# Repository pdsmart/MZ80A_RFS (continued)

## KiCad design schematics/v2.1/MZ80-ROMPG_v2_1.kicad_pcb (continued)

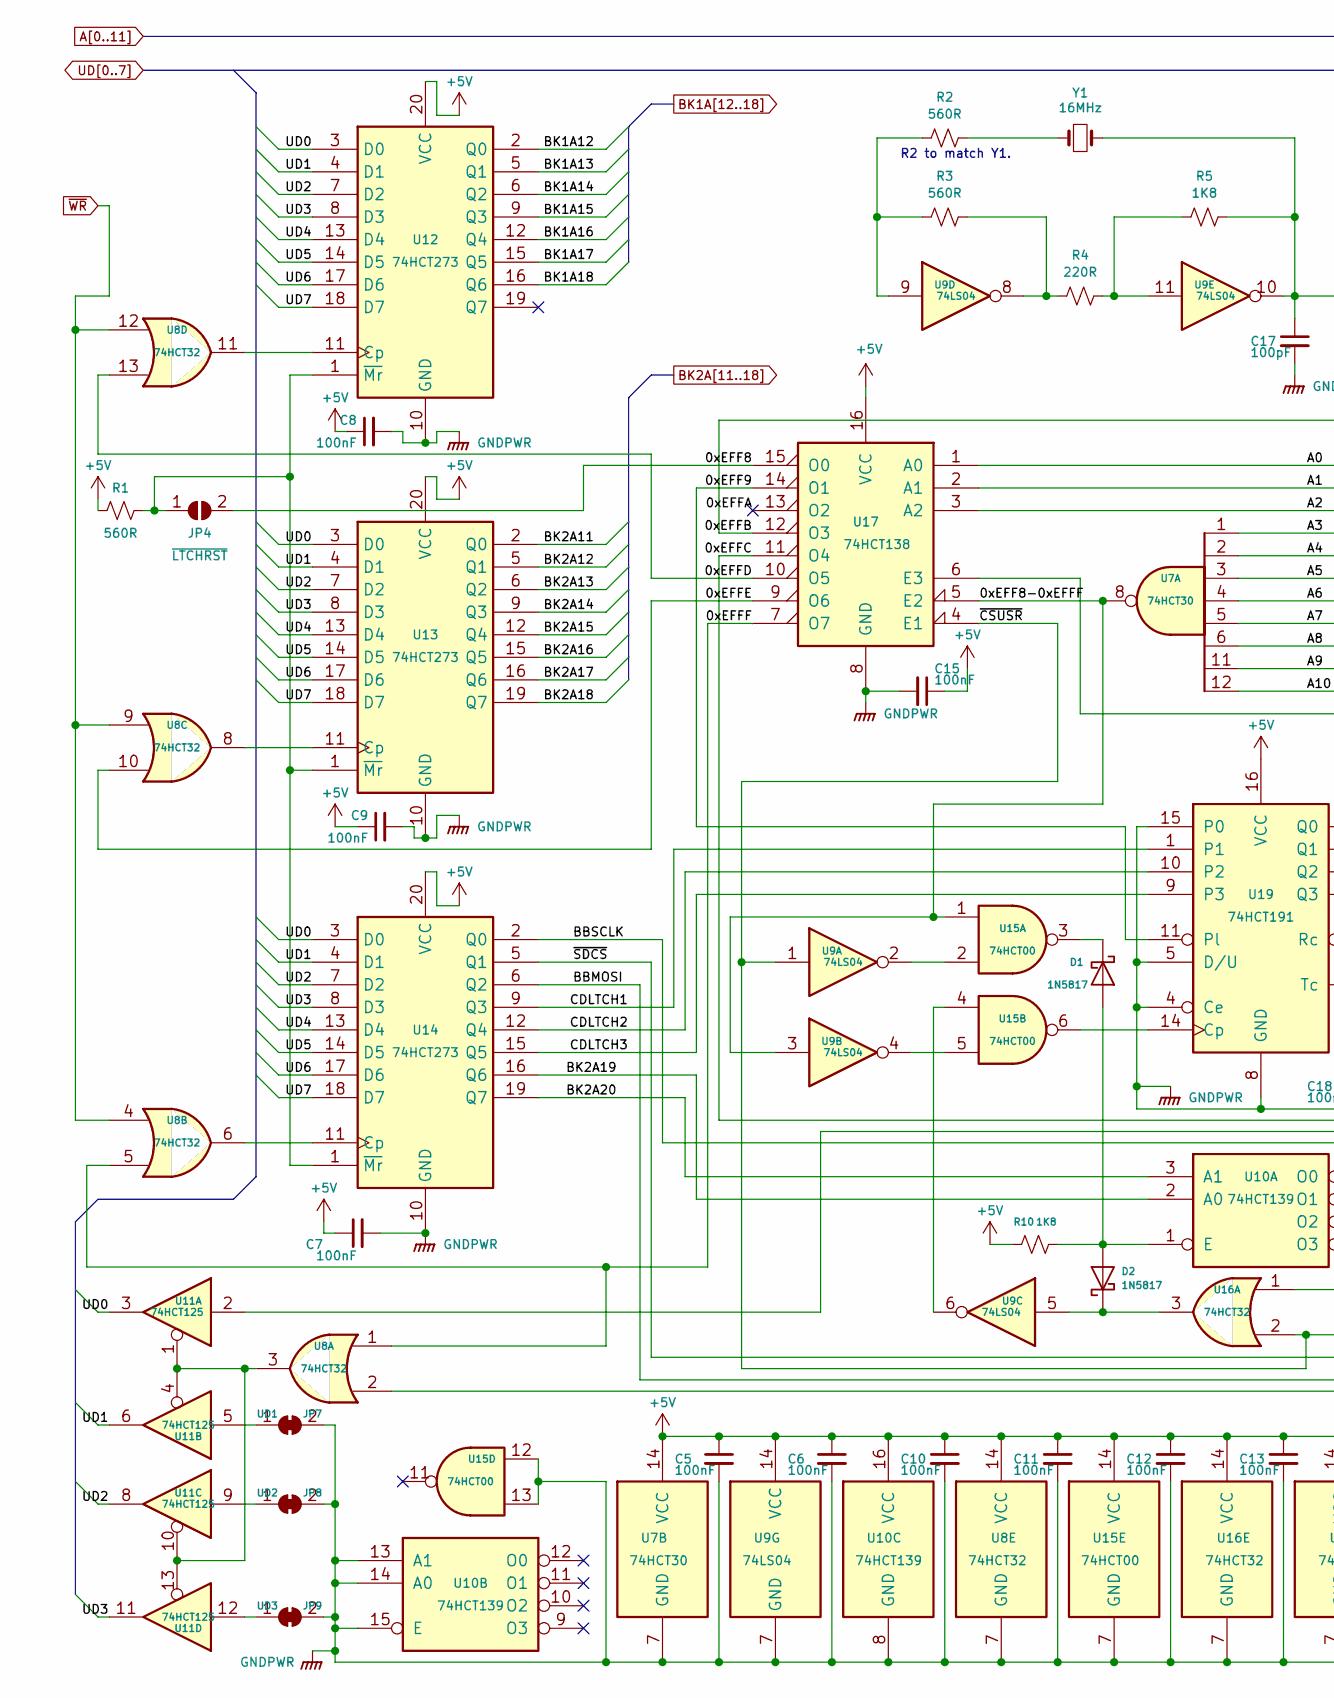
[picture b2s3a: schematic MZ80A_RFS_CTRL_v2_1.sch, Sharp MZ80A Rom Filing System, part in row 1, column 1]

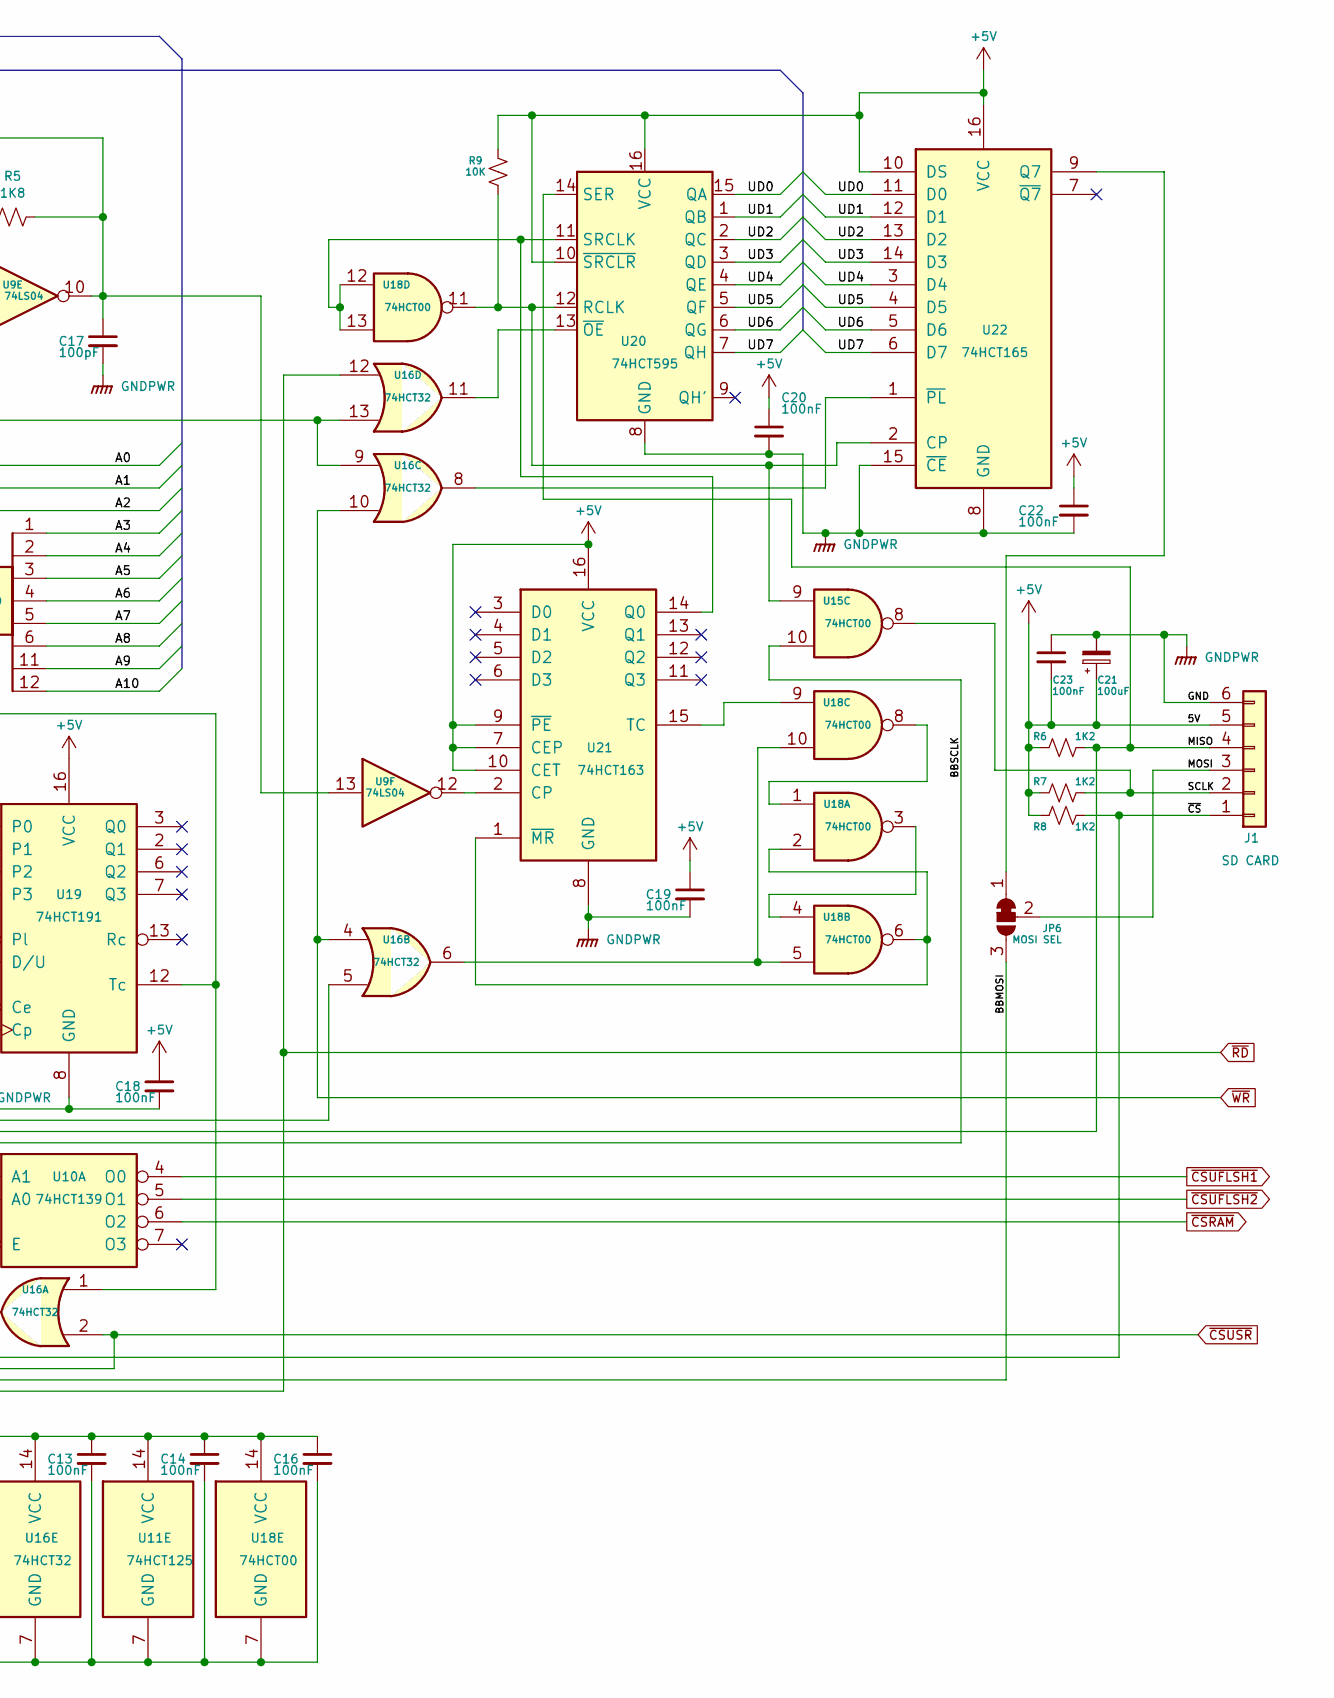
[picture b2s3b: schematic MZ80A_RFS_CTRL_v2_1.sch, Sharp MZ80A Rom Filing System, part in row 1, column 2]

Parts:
C5, C6, C7, C8, C9, C10, C11, C12, C13, C14, C15, C16, C18, C19, C20, C21, C22: 100nF; C_0805_2012Metric_Pad1.15x1.40mm_HandSolder
C17: 100pF; C_0805_2012Metric_Pad1.15x1.40mm_HandSolder
C23: 100uF; C_1206_3216Metric_Pad1.42x1.75mm_HandSolder
D1, D2: 1N5817; D_SOD-123
J1: SD CARD; PinSocket_1x06_P2.54mm_Horizontal
JP4: ~LTCHRST~; SolderJumper-2_P1.3mm_Bridged_Pad1.0x1.5mm
JP6: MOSI SEL; SolderJumper-3_P1.3mm_Bridged2Bar12_Pad1.0x1.5mm
JP7: UD1; SolderJumper-2_P1.3mm_Bridged_Pad1.0x1.5mm
JP8: UD2; SolderJumper-2_P1.3mm_Bridged_Pad1.0x1.5mm
JP9: UD3; SolderJumper-2_P1.3mm_Bridged_Pad1.0x1.5mm
R1, R2, R3: 560R; R_0805_2012Metric_Pad1.15x1.40mm_HandSolder
R4: 220R; R_0805_2012Metric_Pad1.15x1.40mm_HandSolder
R5, R10: 1K8; R_0805_2012Metric_Pad1.15x1.40mm_HandSolder
R6, R7, R8: 1K2; R_0805_2012Metric_Pad1.15x1.40mm_HandSolder
R9: 10K; R_0805_2012Metric_Pad1.15x1.40mm_HandSolder
U7: 74HCT30; SOIC-14_3.9x8.7mm_P1.27mm
U8, U16: 74HCT32; SOIC-14_3.9x8.7mm_P1.27mm
U9: 74LS04; SOIC-14_3.9x8.7mm_P1.27mm
U10: 74HCT139; SOIC-16_3.9x9.9mm_P1.27mm
U11: 74HCT125; SOIC-14_3.9x8.7mm_P1.27mm
U12, U13, U14: 74HCT273; SOIC-20W_7.5x12.8mm_P1.27mm
U15, U18: 74HCT00; SOIC-14_3.9x8.7mm_P1.27mm
U17: 74HCT138; SOIC-16_3.9x9.9mm_P1.27mm
U19: 74HCT191; SOIC-16_3.9x9.9mm_P1.27mm
U20: 74HCT595; SOIC-16_3.9x9.9mm_P1.27mm
U21: 74HCT163; SOIC-16_3.9x9.9mm_P1.27mm
U22: 74HCT165; SOIC-16_3.9x9.9mm_P1.27mm
Y1: 16MHz; Crystal_SMD_Abracon_ABM3-2Pin_5.0x3.2mm

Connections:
+5V: C5.1, C6.1, C7.1, C8.1, C9.1, C10.1, C11.1, C12.1, C13.1, C14.1, C15.1, C16.1, C18.1, C19.1, C20.1, C21.2, C22.1, C23.1, J1.5, R1.2, R6.2, R7.2, R8.2, R9.2, R10.2, U7.14 (VCC), U8.14 (VCC), U9.14 (VCC), U10.16 (VCC), U11.14 (VCC), U12.20 (VCC), U13.20 (VCC), U14.20 (VCC), U15.14 (VCC), U16.14 (VCC), U17.16 (VCC), U18.14 (VCC), U19.16 (VCC), U20.10 (~SRCLR), U20.16 (VCC), U21.7 (CEP), U21.9 (~PE), U21.10 (CET), U21.16 (VCC), U22.10 (DS), U22.16 (VCC); also elsewhere on the board
/CONTROLLOGIC/0xEFF8: JP4.2 (B), U17.15 (O0)
/CONTROLLOGIC/0xEFF8-0xEFFF: U7.8, U9.3, U15.1, U17.5 (E2)
/CONTROLLOGIC/0xEFF9: U17.14 (O1), U19.11 (Pl)
/CONTROLLOGIC/0xEFFA: U17.13 (O2)
/CONTROLLOGIC/0xEFFB: U16.9, U16.13, U17.12 (O3)
/CONTROLLOGIC/0xEFFC: U16.5, U17.11 (O4)
/CONTROLLOGIC/0xEFFD: U8.13, U17.10 (O5)
/CONTROLLOGIC/0xEFFE: U8.10, U17.9 (O6)
/CONTROLLOGIC/0xEFFF: U8.1, U8.5, U17.7 (O7)
/CONTROLLOGIC/BBMOSI: JP6.3 (B), U14.6 (Q2)
/CONTROLLOGIC/BBSCLK: U14.2 (Q0), U15.10
/CONTROLLOGIC/BK2A19: U10.2 (A0), U14.16 (Q6)
/CONTROLLOGIC/BK2A20: U10.3 (A1), U14.19 (Q7)
/CONTROLLOGIC/CDLTCH1: U14.9 (Q3), U19.1
/CONTROLLOGIC/CDLTCH2: U14.12 (Q4), U19.10 (P2)
/CONTROLLOGIC/CDLTCH3: U14.15 (Q5), U19.9 (P3)
/CONTROLLOGIC/MISO: J1.4, R6.1, U11.2, U20.14 (SER)
/CONTROLLOGIC/MOSI: J1.3, JP6.2 (C)
/CONTROLLOGIC/SCLK: J1.2, R7.1, U15.8
/CONTROLLOGIC/~CS~: J1.1, R8.1, U14.5 (Q1)
A0: U17.1 (A0); also elsewhere on the board
A1: U17.2 (A1); also elsewhere on the board
A2: U17.3 (A2); also elsewhere on the board
A3: U7.1; also elsewhere on the board
A4: U7.2; also elsewhere on the board
A5: U7.3; also elsewhere on the board
A6: U7.4; also elsewhere on the board
A7: U7.5; also elsewhere on the board
A8: U7.6; also elsewhere on the board
A9: U7.11; also elsewhere on the board
A10: U7.12; also elsewhere on the board
BK1A12: U12.2 (Q0); also elsewhere on the board
BK1A13: U12.5 (Q1); also elsewhere on the board
BK1A14: U12.6 (Q2); also elsewhere on the board
BK1A15: U12.9 (Q3); also elsewhere on the board
BK1A16: U12.12 (Q4); also elsewhere on the board
BK1A17: U12.15 (Q5); also elsewhere on the board
BK1A18: U12.16 (Q6); also elsewhere on the board
BK2A11: U13.2 (Q0); also elsewhere on the board
BK2A12: U13.5 (Q1); also elsewhere on the board
BK2A13: U13.6 (Q2); also elsewhere on the board
BK2A14: U13.9 (Q3); also elsewhere on the board
BK2A15: U13.12 (Q4); also elsewhere on the board
BK2A16: U13.15 (Q5); also elsewhere on the board
BK2A17: U13.16 (Q6); also elsewhere on the board
BK2A18: U13.19 (Q7); also elsewhere on the board
GNDPWR: C5.2, C6.2, C7.2, C8.2, C9.2, C10.2, C11.2, C12.2, C13.2, C14.2, C15.2, C16.2, C17.2, C18.2, C19.2, C20.2, C21.1, C22.2, C23.2, J1.6, JP7.2 (B), JP8.2 (B), JP9.2 (B), U7.7 (GND), U8.7 (GND), U9.7 (GND), U10.8 (GND), U10.13 (A1), U10.14 (A0), U10.15 (E), U11.7 (GND), U12.10 (GND), U13.10 (GND), U14.10 (GND), U15.7 (GND), U15.12, U15.13, U16.7 (GND), U17.8 (GND), U18.7 (GND), U19.4 (Ce), U19.5 (D/U), U19.8 (GND), U19.15 (P0), U20.8 (GND), U21.8 (GND), U22.8 (GND), U22.15 (~CE); also elsewhere on the board
unnamed: C17.1, R5.1, U9.10, U9.13, Y1.2
unnamed: D1.1 (K), U15.3
unnamed: D1.2 (A), D2.2 (A), R10.1, U10.1 (E)
unnamed: D2.1 (K), U9.5, U16.3
unnamed: JP4.1 (A), R1.1, U12.1 (~Mr), U13.1 (~Mr), U14.1 (~Mr)
unnamed: JP6.1 (A), U22.9 (Q7)
unnamed: JP7.1 (A), U11.5
unnamed: JP8.1 (A), U11.9
unnamed: JP9.1 (A), U11.12
unnamed: R2.1, Y1.1
unnamed: R2.2, R3.2, U9.9
unnamed: R3.1, R4.2, U9.8
unnamed: R4.1, R5.2, U9.11
unnamed: R9.1, U15.9, U18.11, U20.12 (RCLK), U22.2 (CP)
unnamed: U8.3, U11.1, U11.4, U11.10, U11.13
unnamed: U8.11, U12.11 (Cp)
unnamed: U8.8, U13.11 (Cp)
unnamed: U8.6, U14.11 (Cp)
unnamed: U9.2, U15.2
unnamed: U9.6, U15.4
unnamed: U9.4, U15.5
unnamed: U15.6, U19.14 (Cp)
unnamed: U16.1, U17.6 (E3), U19.12 (Tc)
unnamed: U16.6, U18.5, U18.10
unnamed: U16.8, U22.1 (~PL)
unnamed: U16.11, U20.13 (~OE)
unnamed: U18.1, U18.8
unnamed: U18.2, U18.6, U21.1 (~MR)
unnamed: U18.3, U18.4
unnamed: U18.9, U21.15 (TC)
unnamed: U18.12, U18.13, U20.11 (SRCLK), U21.14 (Q0)
unnamed: U9.12, U21.2 (CP)
UD0: U11.3, U12.3 (D0), U13.3 (D0), U14.3 (D0), U20.15 (QA), U22.11 (D0); also elsewhere on the board
UD1: U11.6, U12.4 (D1), U13.4 (D1), U14.4 (D1), U20.1 (QB), U22.12 (D1); also elsewhere on the board
UD2: U11.8, U12.7 (D2), U13.7 (D2), U14.7 (D2), U20.2 (QC), U22.13 (D2); also elsewhere on the board
UD3: U11.11, U12.8 (D3), U13.8 (D3), U14.8 (D3), U20.3 (QD), U22.14 (D3); also elsewhere on the board
UD4: U12.13 (D4), U13.13 (D4), U14.13 (D4), U20.4 (QE), U22.3 (D4); also elsewhere on the board
UD5: U12.14 (D5), U13.14 (D5), U14.14 (D5), U20.5 (QF), U22.4 (D5); also elsewhere on the board
UD6: U12.17 (D6), U13.17 (D6), U14.17 (D6), U20.6 (QG), U22.5 (D6); also elsewhere on the board
UD7: U12.18 (D7), U13.18 (D7), U14.18 (D7), U20.7 (QH), U22.6 (D7); also elsewhere on the board
~CSRAM~: U10.6 (O2); also elsewhere on the board
~CSUFLSH1~: U10.4 (O0); also elsewhere on the board
~CSUFLSH2~: U10.5 (O1); also elsewhere on the board
~CSUSR~: U9.1, U16.2, U17.4 (E1); also elsewhere on the board
~RD~: U8.2, U16.12; also elsewhere on the board
~WR~: U8.4, U8.9, U8.12, U16.4, U16.10; also elsewhere on the board

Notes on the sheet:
R2 to match Y1.

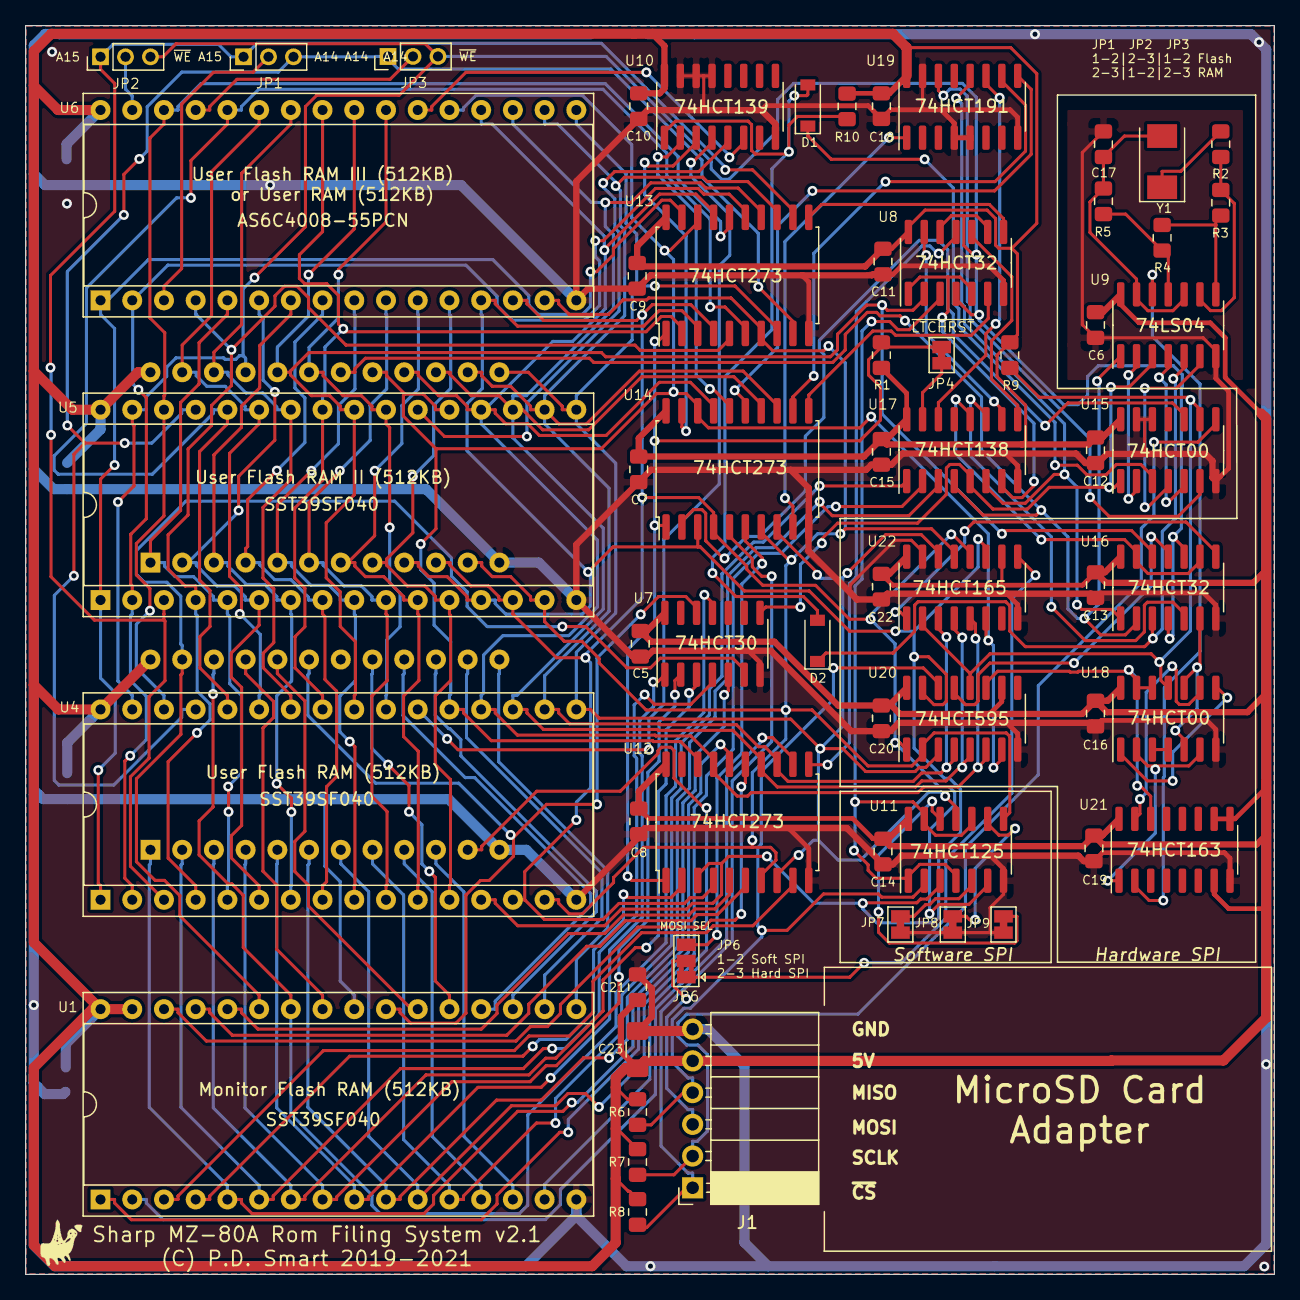
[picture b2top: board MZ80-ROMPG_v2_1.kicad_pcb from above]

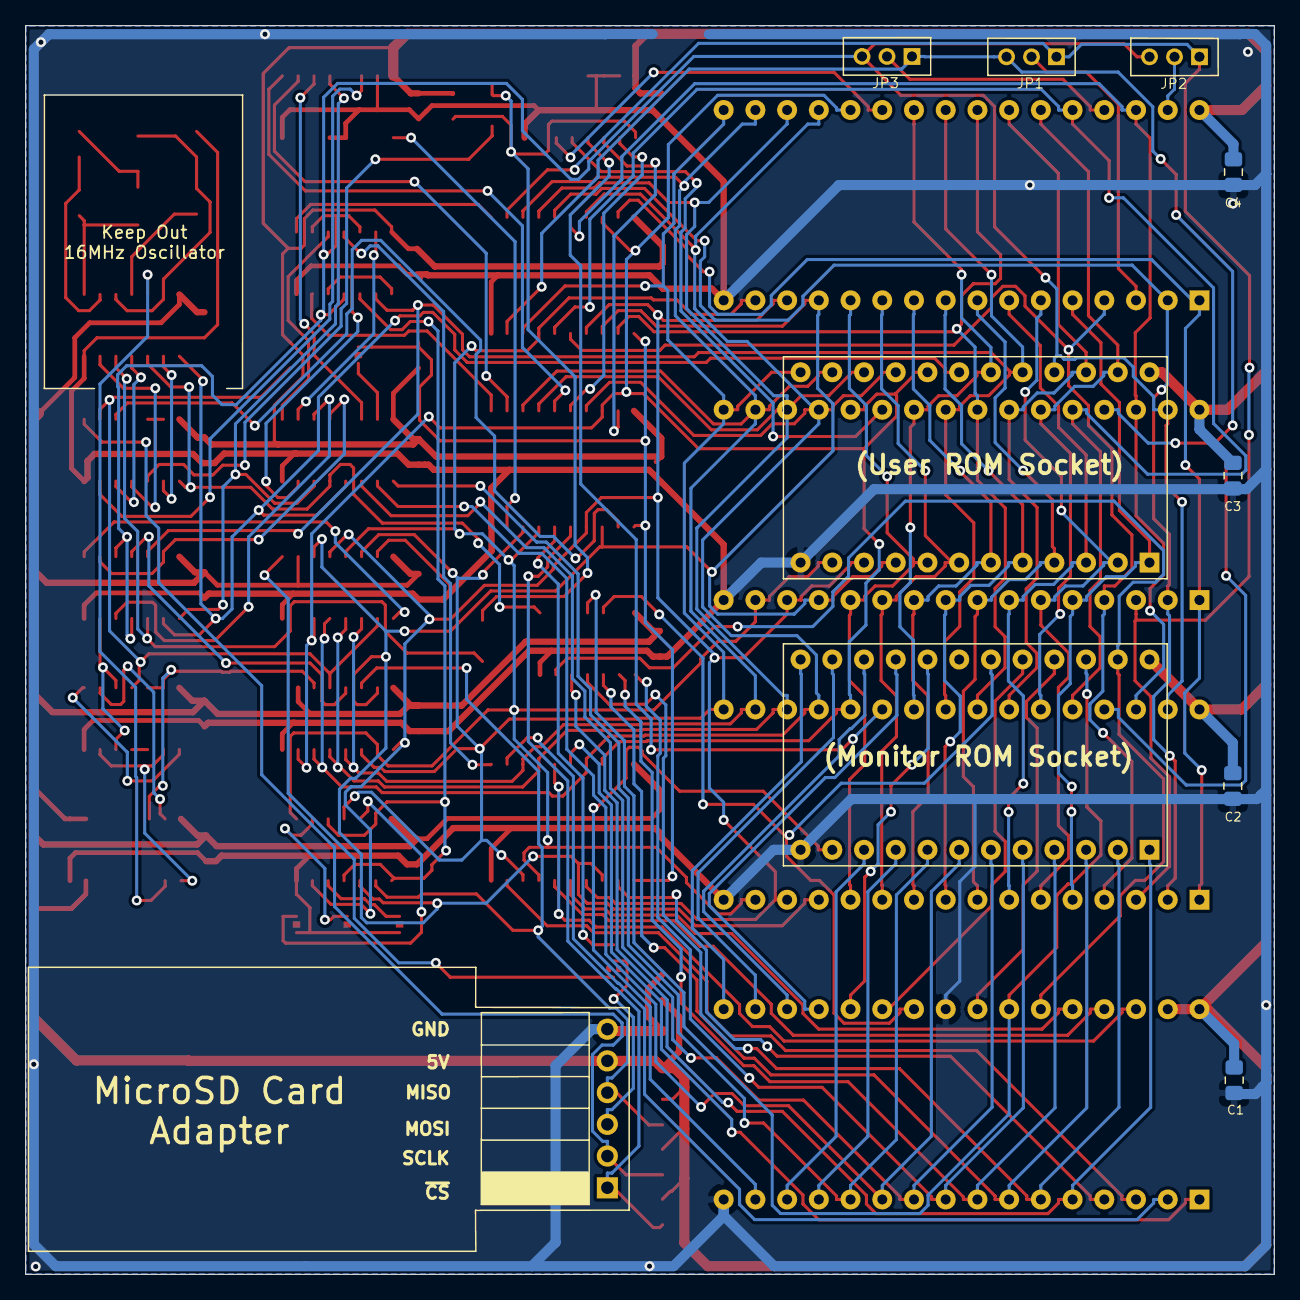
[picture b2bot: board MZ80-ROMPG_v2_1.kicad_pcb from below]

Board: 2 copper layers, 100.0 x 100.0 mm, 68 parts (4 on the bottom side), 117 nets.

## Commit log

2019-10-25 First push
2019-10-26 Missing tools
2019-11-11 Pictures of RFS running
2019-11-11 Set theme jekyll-theme-tactile
2020-02-25 Updates to add CPM and other changes
2020-02-29 Remove temp files
2020-02-29 Bug fixes
2020-03-02 Attributes
2020-03-03 Added Multicomp disks in MZ80A format and a build script
2020-03-03 LFS update
2020-03-03 Updates to CPM programs
2020-03-07 Made it easier to build the rom drive
2020-03-11 Added interrupt driven keyboard buffer with autorepeat Interrupt driven cursor flash with NO, CAPS and SHIFTLOCK modes. Optimised some of the code and removed redundancies
2020-03-18 Updates due to adding SD Card
2020-03-23 SD Card updates for CPM
2020-03-23 SD Card images
2020-03-24 Removed temp files
2020-03-27 Updated and added SD to/from Tape copy commands and SD erase
2020-03-27 Bug introduced when converting to common messages
2020-04-03 Added v2 PCB details
2020-04-03 Images
2020-05-12 Updated to v2 hardware, working as per v1. Need to add the additional ROM, RAM and enable writes to the Flash RAM
2020-05-14 Solved CPM boot hang, uninitialised memory so now on cold boot all memory is initialised. Also added 320K ROM drive definitions.
2020-05-15 Updates so ROM drives are fixed drives, saves some RAM.
2020-05-15 Minor schematic update
2020-06-02 Potential issues seen, comments added
2020-07-12 Updated to use CMT
2020-07-24 Bug fixes and changes to coexist with the tranZPUterSW v2.1
2020-07-29 Updates for v2.1 of the tranZPUter board and bug fixes
2021-02-06 Added schematics, kicad and pcb gerber files
2021-02-18 Re-organisation of CAD files, previous version not useable as files missing
2021-02-19 Tidy
2021-03-03 Removed files which shouldnt be on git
2021-04-04 RFS updates for SA-5510 Basic, added SD commands for Load,Save,Dir
2021-04-06 Updates MSBASIC with CLOAD/CSAVE/DIR for SD Card access under RFS.
2021-04-11 Updated CPM, removed ROM Drives, updated BASIC and RFS
2021-04-11 Directory rename
2021-04-18 Updates and 40/80 compilation modes
2021-04-25 Updates to MSBASIC for 40/80 column modes
2021-05-04 Timing related SD card initialisation bug, new board release can fail to initialise and loop.
    Former-commit-id: 5d6bcf94519d17176fd17db1cd82387cd8454f65
2021-05-04 Timing related SD card initialisation bug, new board release can fail to initialise and loop.
2021-05-04 Added release binaries
    Former-commit-id: 7b1dfe8ba2729db02ae19f875459fd8fbed319a7
2021-05-04 Added release binaries
2021-05-04 Releases too large for github
2021-05-04 Releases too large for github
    Former-commit-id: ad341173863b673ba554c2a89a19afe557a596fd
2021-05-04 test
2021-05-04 test reversal
2021-05-10 Fixed timing issues with differing motherboards and RFS boards
2021-08-22 Updates after feedback and differing hardware platform states
2023-02-23 Moved RFS software to a seperate repository as it is now used by tzpuFusionX as well as the RFS hardware board.
2023-02-23 Sync issue
2023-02-23 Minor updates, some due to perl changes, discovered during FusionX port
